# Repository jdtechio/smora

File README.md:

## SMORA

> [Development Blog](http://smora.jdtech.io/)

> Modified from [Minimal Mistakes Jekyll Theme](https://github.com/mmistakes/minimal-mistakes/)

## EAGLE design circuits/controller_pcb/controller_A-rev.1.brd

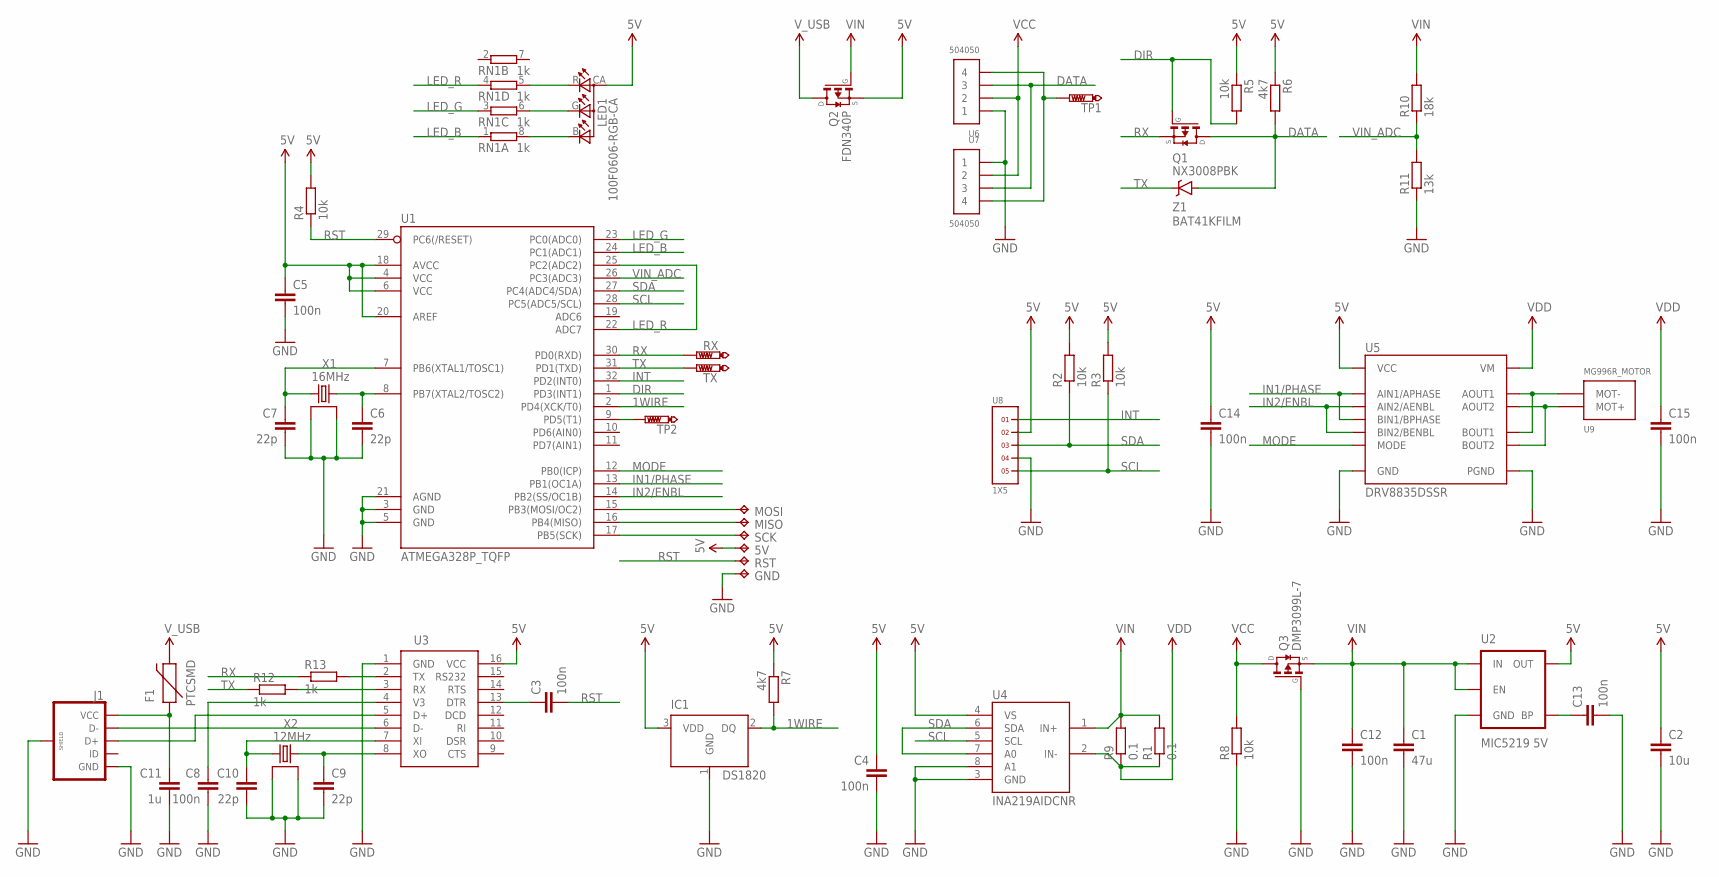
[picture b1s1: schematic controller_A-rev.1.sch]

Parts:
5V: TPTP07SQ; TP07SQ
C1: 47u; C1206
C2: 10u; C0603K
C3, C4, C5, C8, C12, C13, C14, C15: 100n; C0402K
C6, C7, C9, C10: 22p; C0402K
C11: 1u; C0402K
F1: PTCSMD; PTC-1206
GND: TPTP07SQ; TP07SQ
IC1: DS1820; TO-92
J1: USB_MICROB_PLUGCONN-11752; USB-B-MICRO-SMD_V03
LED1: 100F0606-RGB-CA; 1616
MISO: TPTP07SQ; TP07SQ
MOSI: TPTP07SQ; TP07SQ
Q1: NX3008PBK; SSOT-3
Q2: FDN340P; SSOT-3
Q3: DMP3099L-7; SOT23
R1: 0.1; R0603
R2, R3, R4, R5, R8: 10k; R0402
R6, R7: 4k7; R0402
R9: 0.1; R2512
R10: 18k; R0402
R11: 13k; R0402
R12, R13: 1k; R0402
RN1: 1k; YC124
RST: TPTP07SQ; TP07SQ
RX: PTR1TP10R; TP10R
SCK: TPTP07SQ; TP07SQ
TP1, TP2: PTR1TP10R; TP10R
TX: PTR1TP10R; TP10R
U1: ATMEGA328P_TQFP; TQFP32-08
U2: MIC5219 5V; SOT23-5
U3: CH340G; SOIC16
U4: INA219AIDCNR; SOT23-8L
U5: DRV8835DSSR; WSON-12
U6, U7: 504050
U8: 1X5
U9: MG996R_MOTOR; MOTOR
X1: 16MHz; OSC3225
X2: 12MHz; OSC3225
Z1: BAT41KFILM; SOD-523

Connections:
1WIRE: IC1.2 (DQ), R7.2, U1.2 (PD4(XCK/T0))
5V: 5V.TP, C2.1, C4.1, C5.1, C14.1, IC1.3 (VDD), LED1.CA, Q2.2 (S), R2.2, R3.2, R4.2, R5.1, R6.1, R7.1, U1.4 (VCC), U1.6 (VCC), U1.18 (AVCC), U1.20 (AREF), U2.5 (OUT), U3.16 (VCC), U4.4 (VS), U5.P$12 (VCC), U8.2
AUX: TP1.TP, U6.P$4 (4), U7.P$4 (4)
D+: J1.D+, U3.5 (D+)
D-: J1.D-, U3.6 (D-)
DATA: Q1.3 (D), R6.2, U6.P$3 (3), U7.P$3 (3), Z1.P$1 (1)
DIR: Q1.1 (G), R5.2, U1.1 (PD3(INT1))
GND: C1.2, C2.2, C4.2, C5.2, C6.2, C7.2, C8.2, C9.2, C10.2, C11.2, C12.2, C13.2, C14.2, C15.2, GND.TP, IC1.1 (GND), J1.GND, J1.SHIELD1 (SHIELD), J1.SHIELD2 (SHIELD), J1.SHIELD3 (SHIELD), Q3.1 (G), R8.1, R11.1, U1.3 (GND), U1.5 (GND), U1.21 (AGND), U2.2 (GND), U3.1 (GND), U4.3 (GND), U4.8 (A1), U5.P$6 (GND), U5.P$13 (PGND), U5.P$14 (PGND), U5.P$15 (PGND), U5.P$16 (PGND), U6.P$1 (1), U7.P$1 (1), U8.4, X1.P$2 (2), X1.P$4 (4), X2.P$2 (2), X2.P$4 (4)
IN1/PHASE: U1.13 (PB1(OC1A)), U5.P$8 (BIN1/BPHASE), U5.P$10 (AIN1/APHASE)
IN2/ENBL: U1.14 (PB2(SS/OC1B)), U5.P$7 (BIN2/BENBL), U5.P$9 (AIN2/AENBL)
INT: U1.32 (PD2(INT0)), U8.1
LED_B: RN1.1, U1.24 (PC1(ADC1))
LED_B_: LED1.B, RN1.8 (2)
LED_G: RN1.3 (1), U1.23 (PC0(ADC0))
LED_G_: LED1.G, RN1.6 (2)
LED_R: RN1.4 (1), U1.22 (ADC7), U1.25 (PC2(ADC2))
LED_R_: LED1.R, RN1.5 (2)
MODE: U1.12 (PB0(ICP)), U5.P$11 (MODE)
MOT+: U5.P$2 (AOUT1), U5.P$4 (BOUT1), U9.P$3 (MOT-), U9.P$4 (MOT-)
MOT-: U5.P$3 (AOUT2), U5.P$5 (BOUT2), U9.P$1 (MOT+), U9.P$2 (MOT+)
unnamed: C6.1, U1.8 (PB7(XTAL2/TOSC2)), X1.P$1 (1)
unnamed: C7.1, U1.7 (PB6(XTAL1/TOSC1)), X1.P$3 (3)
unnamed: MOSI.TP, U1.15 (PB3(MOSI/OC2))
unnamed: MISO.TP, U1.16 (PB4(MISO))
unnamed: C3.1, U3.13 (DTR)
unnamed: R13.2, U3.2 (TX)
unnamed: C10.1, U3.7 (XI), X2.P$3 (3)
unnamed: C9.1, U3.8 (XO), X2.P$1 (1)
unnamed: C11.1, F1.1, J1.VBUS (VCC)
unnamed: C8.1, U3.4 (V3)
unnamed: C13.1, U2.4 (BP)
unnamed: TP2.TP, U1.9 (PD5(T1))
unnamed: SCK.TP, U1.17 (PB5(SCK))
unnamed: R12.2, U3.3 (RX)
RST: C3.2, R4.1, RST.TP, U1.29 (PC6(/RESET))
RX: Q1.2 (S), R13.1, RX.TP, U1.30 (PD0(RXD))
SCL: R3.1, U1.28 (PC5(ADC5/SCL)), U4.5 (SCL), U8.5
SDA: R2.1, U1.27 (PC4(ADC4/SDA)), U4.6 (SDA), U4.7 (A0), U8.3
TX: R12.1, TX.TP, U1.31 (PD1(TXD)), Z1.P$2 (2)
VCC: Q3.3 (D), R8.2, U6.P$2 (2), U7.P$2 (2)
VDD: C15.1, R1.1, R9.1, U4.2 (IN-), U5.P$1 (VM)
VIN: C1.1, C12.1, Q2.1 (G), Q3.2 (S), R1.2, R9.2, R10.2, U2.1 (IN), U2.3 (EN), U4.1 (IN+)
VIN_ADC: R10.1, R11.2, U1.26 (PC3(ADC3))
V_USB: F1.2, Q2.3 (D)

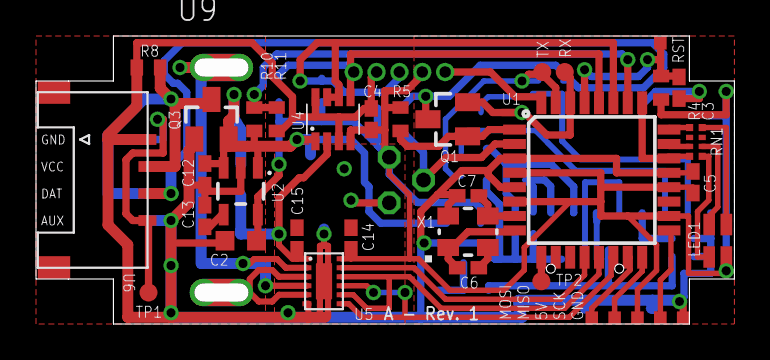
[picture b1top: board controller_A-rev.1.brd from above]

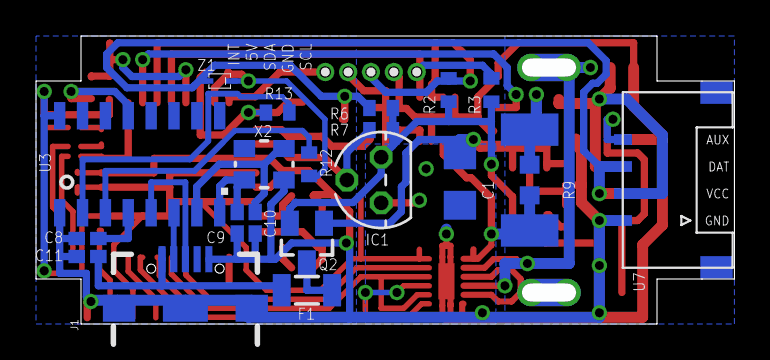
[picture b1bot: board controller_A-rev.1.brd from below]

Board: 2 copper layers, 37.8 x 15.0 mm, 58 parts (22 on the bottom side), 44 nets.

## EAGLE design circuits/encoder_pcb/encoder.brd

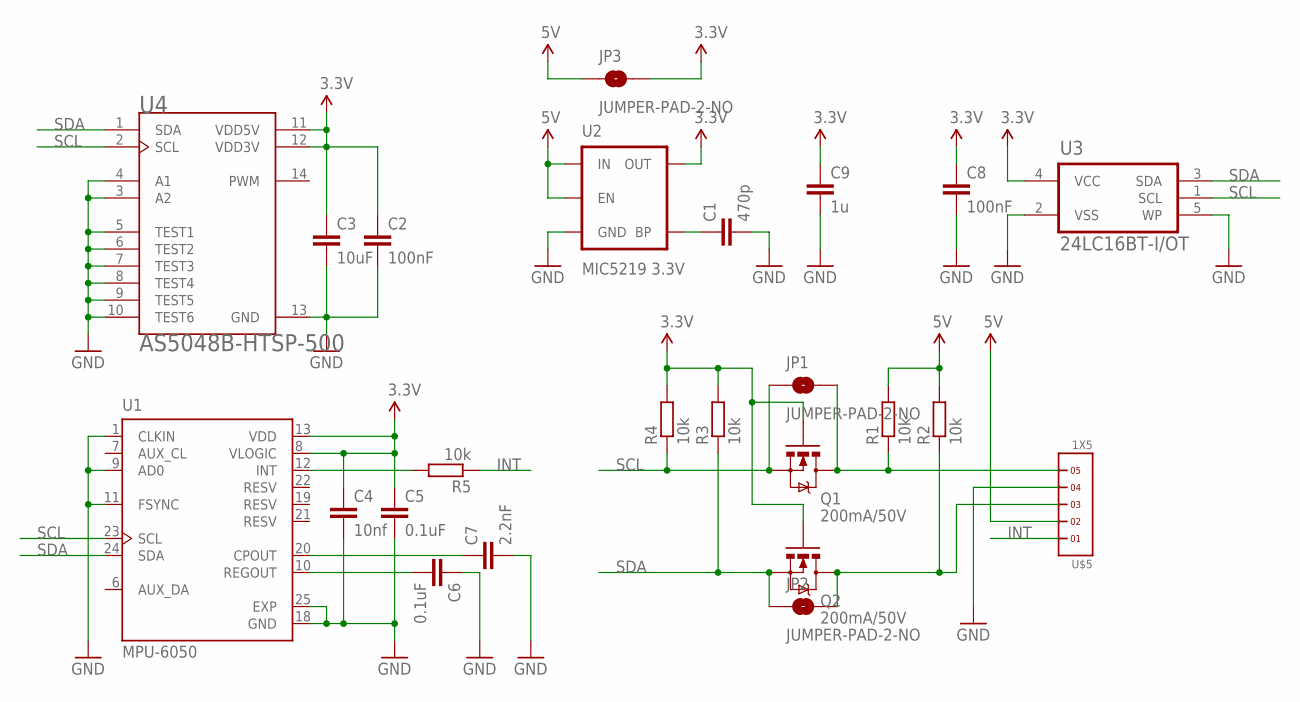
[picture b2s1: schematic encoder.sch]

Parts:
C1: 470p; C0402K
C2, C8: 100nF; C0402K
C3: 10uF; C0603K
C4: 10nf; C0402K
C5, C6: 0.1uF; C0402K
C7: 2.2nF; C0402K
C9: 1u; C0402K
JP1, JP2, JP3: JUMPER-PAD-2-NO; PAD-JUMPER-2-NO_NO_SILK
Q1, Q2: 200mA/50V; SOT23-3
R1, R2, R3, R4, R5: 10k; R0402
U1: MPU-6050; QFN50P400X400X95-25N
U2: MIC5219 3.3V; SOT23-5
U3: 24LC16BT-I/OT; SOT-23-5
U4: AS5048B-HTSP-500; SOP65P640X120-14N
U$5: 1X5

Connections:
3.3V: C2.1, C3.1, C4.1, C5.1, C8.1, C9.1, JP3.2, Q1.1 (G), Q2.1 (G), R3.2, R4.2, U1.8 (VLOGIC), U1.13 (VDD), U2.5 (OUT), U3.4 (VCC), U4.11 (VDD5V), U4.12 (VDD3V)
5V: JP3.1, R1.2, R2.2, U2.1 (IN), U2.3 (EN), U$5.2
GND: C1.2, C2.2, C3.2, C4.2, C5.2, C6.1, C7.2, C8.2, C9.2, U1.1 (CLKIN), U1.9 (AD0), U1.11 (FSYNC), U1.18 (GND), U1.25 (EXP), U2.2 (GND), U3.2 (VSS), U3.5 (WP), U4.3 (A2), U4.4 (A1), U4.5 (TEST1), U4.6 (TEST2), U4.7 (TEST3), U4.8 (TEST4), U4.9 (TEST5), U4.10 (TEST6), U4.13 (GND), U$5.4
INT: R5.1, U$5.1
unnamed: C1.1, U2.4 (BP)
unnamed: C7.1, U1.20 (CPOUT)
unnamed: R5.2, U1.12 (INT)
unnamed: C6.2, U1.10 (REGOUT)
SCL: JP1.1, Q1.2 (S), R4.1, U1.23 (SCL), U3.1 (SCL), U4.2 (SCL)
SCL_: JP1.2, Q1.3 (D), R1.1, U$5.5
SDA: JP2.1, Q2.2 (S), R3.1, U1.24 (SDA), U3.3 (SDA), U4.1 (SDA)
SDA_: JP2.2, Q2.3 (D), R2.1, U$5.3

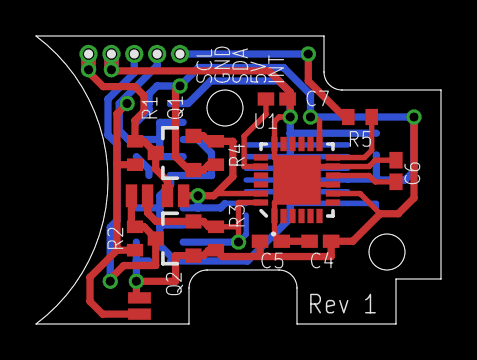
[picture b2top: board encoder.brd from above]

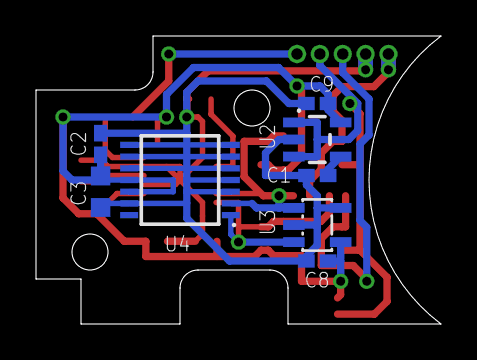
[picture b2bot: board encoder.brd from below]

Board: 2 copper layers, 22.5 x 16.0 mm, 24 parts (8 on the bottom side), 12 nets.

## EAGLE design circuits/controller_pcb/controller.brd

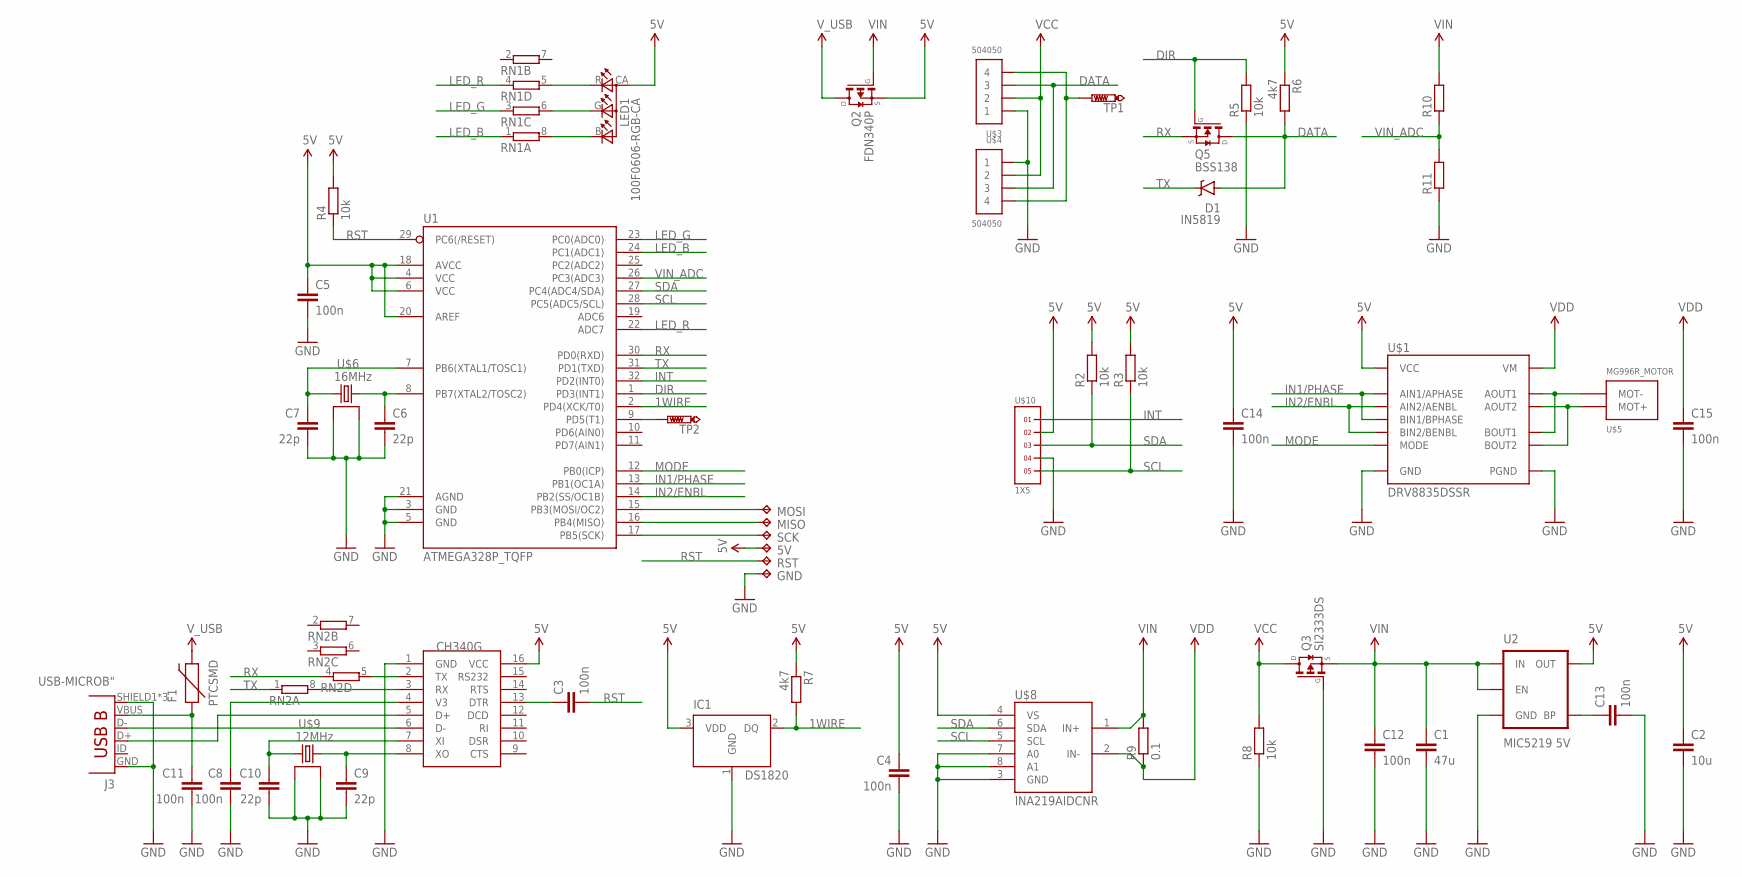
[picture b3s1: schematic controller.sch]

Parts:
5V: TPTP07SQ; TP07SQ
C1: 47u; C1206
C2: 10u; C0603K
C3, C4, C5, C8, C11, C12, C13, C14, C15: 100n; C0402K
C6, C7, C9, C10: 22p; C0402K
D1: IN5819; SMA-DIODE
F1: PTCSMD; PTC-1206
GND: TPTP07SQ; TP07SQ
IC1: DS1820; TO-92
J3: USB-MICROB"; USB-B-MICRO-SMD_V03
LED1: 100F0606-RGB-CA; 1616
MISO: TPTP07SQ; TP07SQ
MOSI: TPTP07SQ; TP07SQ
Q2: FDN340P; SSOT-3
Q3: SI2333DS; SOT23
Q5: BSS138; SOT23
R2, R3, R4, R5, R8: 10k; R0402
R6, R7: 4k7; R0402
R9: 0.1; R2512
R10, R11: R-EU_R0402; R0402
RN1, RN2: 4R-NYC124; YC124
RST: TPTP07SQ; TP07SQ
SCK: TPTP07SQ; TP07SQ
TP1, TP2: PTR1TP12R; TP12R
U1: ATMEGA328P_TQFP; TQFP32-08
U2: MIC5219 5V; SOT23-5
U$1: DRV8835DSSR; WSON-12
U$2: CH340G; SOIC16
U$3, U$4: 504050
U$5: MG996R_MOTOR; MOTOR
U$6: 16MHz; OSC3225
U$8: INA219AIDCNR; SOT23-8L
U$9: 12MHz; OSC3225
U$10: 1X5

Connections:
1WIRE: IC1.2 (DQ), R7.2, U1.2 (PD4(XCK/T0))
5V: 5V.TP, C2.1, C4.1, C5.1, C14.1, IC1.3 (VDD), LED1.CA, Q2.2 (S), R2.2, R3.2, R4.2, R6.1, R7.1, U1.4 (VCC), U1.6 (VCC), U1.18 (AVCC), U1.20 (AREF), U2.5 (OUT), U$1.P$12 (VCC), U$2.16 (VCC), U$8.4 (VS), U$10.2
D+: J3.D+, U$2.5 (D+)
D-: J3.D-, U$2.6 (D-)
DATA: D1.A, Q5.3 (D), R6.2, U$3.P$3 (3), U$4.P$3 (3)
DIR: Q5.1 (G), R5.2, U1.1 (PD3(INT1))
GND: C1.2, C2.2, C4.2, C5.2, C6.2, C7.2, C8.2, C9.2, C10.2, C11.2, C12.2, C13.2, C14.2, C15.2, GND.TP, IC1.1 (GND), J3.GND, J3.SHIELD1 (SHIELD), J3.SHIELD2 (SHIELD), J3.SHIELD3 (SHIELD), Q3.1 (G), R5.1, R8.1, R11.1, U1.3 (GND), U1.5 (GND), U1.21 (AGND), U2.2 (GND), U$1.P$6 (GND), U$1.P$13 (PGND), U$1.P$14 (PGND), U$1.P$15 (PGND), U$1.P$16 (PGND), U$2.1 (GND), U$3.P$1 (1), U$4.P$1 (1), U$6.P$2 (2), U$6.P$4 (4), U$8.3 (GND), U$8.7 (A0), U$8.8 (A1), U$9.P$2 (2), U$9.P$4 (4), U$10.4
IN1/PHASE: U1.13 (PB1(OC1A)), U$1.P$8 (BIN1/BPHASE), U$1.P$10 (AIN1/APHASE)
IN2/ENBL: U1.14 (PB2(SS/OC1B)), U$1.P$7 (BIN2/BENBL), U$1.P$9 (AIN2/AENBL)
INT: U1.32 (PD2(INT0)), U$10.1
LED_B: RN1.1, U1.24 (PC1(ADC1))
LED_B_: LED1.B, RN1.8 (2)
LED_G: RN1.3 (1), U1.23 (PC0(ADC0))
LED_G_: LED1.G, RN1.6 (2)
LED_R: RN1.4 (1), U1.22 (ADC7)
LED_R_: LED1.R, RN1.5 (2)
MODE: U1.12 (PB0(ICP)), U$1.P$11 (MODE)
MOT+: U$1.P$2 (AOUT1), U$1.P$4 (BOUT1), U$5.P$3 (MOT-), U$5.P$4 (MOT-)
MOT-: U$1.P$3 (AOUT2), U$1.P$5 (BOUT2), U$5.P$1 (MOT+), U$5.P$2 (MOT+)
unnamed: C6.1, U1.8 (PB7(XTAL2/TOSC2)), U$6.P$1 (1)
unnamed: C7.1, U1.7 (PB6(XTAL1/TOSC1)), U$6.P$3 (3)
unnamed: MOSI.TP, U1.15 (PB3(MOSI/OC2))
unnamed: MISO.TP, U1.16 (PB4(MISO))
unnamed: C3.1, U$2.13 (DTR)
unnamed: RN2.5 (2), U$2.2 (TX)
unnamed: TP1.TP, U$3.P$4 (4), U$4.P$4 (4)
unnamed: C10.1, U$2.7 (XI), U$9.P$3 (3)
unnamed: C9.1, U$2.8 (XO), U$9.P$1 (1)
unnamed: C11.1, F1.1, J3.VBUS
unnamed: C8.1, U$2.4 (V3)
unnamed: C13.1, U2.4 (BP)
unnamed: TP2.TP, U1.9 (PD5(T1))
unnamed: SCK.TP, U1.17 (PB5(SCK))
unnamed: RN2.8 (2), U$2.3 (RX)
RST: C3.2, R4.1, RST.TP, U1.29 (PC6(/RESET))
RX: Q5.2 (S), RN2.4 (1), U1.30 (PD0(RXD))
SCL: R3.1, U1.28 (PC5(ADC5/SCL)), U$8.5 (SCL), U$10.5
SDA: R2.1, U1.27 (PC4(ADC4/SDA)), U$8.6 (SDA), U$10.3
TX: D1.C, RN2.1, U1.31 (PD1(TXD))
VCC: Q3.3 (D), R8.2, U$3.P$2 (2), U$4.P$2 (2)
VDD: C15.1, R9.1, U$1.P$1 (VM), U$8.2 (IN-)
VIN: C1.1, C12.1, Q2.1 (G), Q3.2 (S), R9.2, R10.2, U2.1 (IN), U2.3 (EN), U$8.1 (IN+)
VIN_ADC: R10.1, R11.2, U1.26 (PC3(ADC3))
V_USB: F1.2, Q2.3 (D)

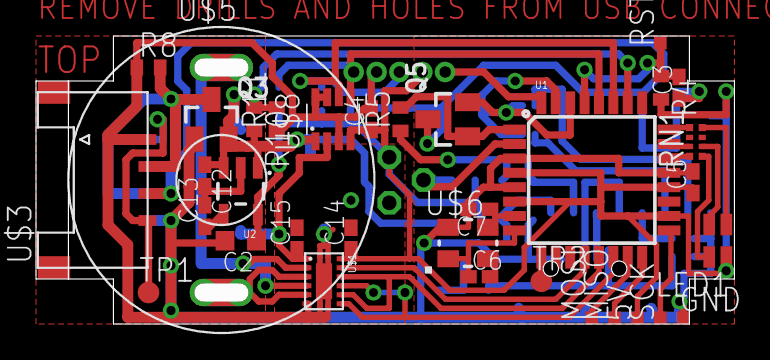
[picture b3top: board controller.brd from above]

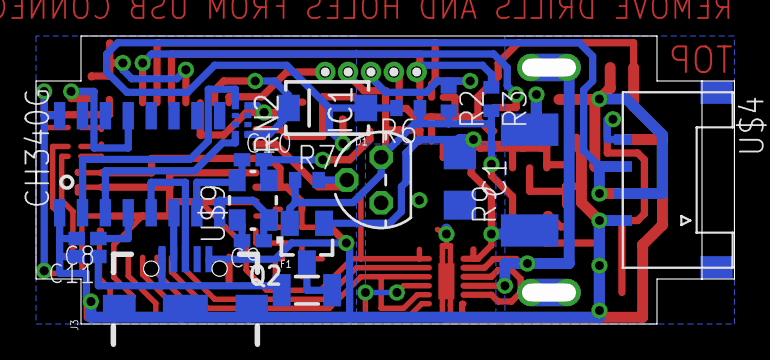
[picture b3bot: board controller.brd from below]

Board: 2 copper layers, 37.8 x 15.0 mm, 54 parts (20 on the bottom side), 44 nets.

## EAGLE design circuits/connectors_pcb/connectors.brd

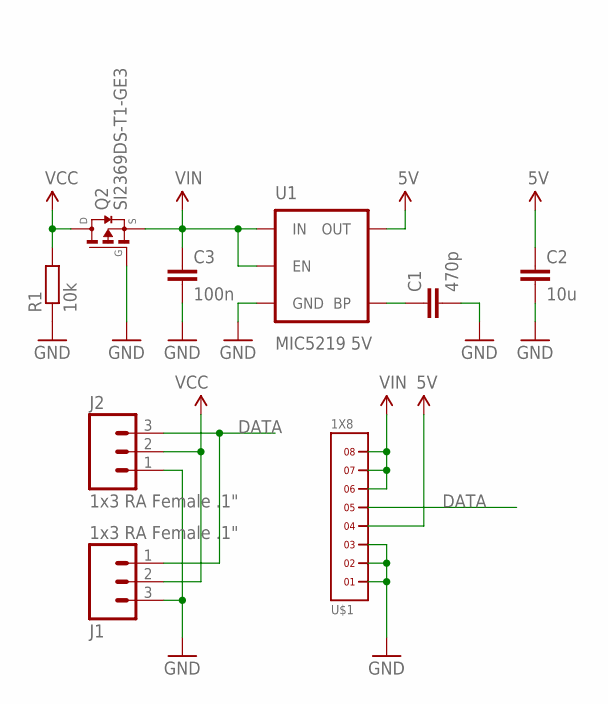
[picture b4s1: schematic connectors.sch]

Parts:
C1: 470p; C0402K
C2: 10u; C0603K
C3: 100n; C0402K
J1, J2: 1x3 RA Female .1"; 1X03_SMD_RA_FEMALE
Q2: SI2369DS-T1-GE3; SOT23
R1: 10k; R0603
U1: MIC5219 5V; SOT23-5
U$1: 1X8

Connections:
5V: C2.1, U1.5 (OUT), U$1.4
DATA: J1.1, J2.3, U$1.5
GND: C1.2, C2.2, C3.2, J1.3, J2.1, Q2.1 (G), R1.1, U1.2 (GND), U$1.1, U$1.2, U$1.3
unnamed: C1.1, U1.4 (BP)
VCC: J1.2, J2.2, Q2.3 (D), R1.2
VIN: C3.1, Q2.2 (S), U1.1 (IN), U1.3 (EN), U$1.6, U$1.7, U$1.8

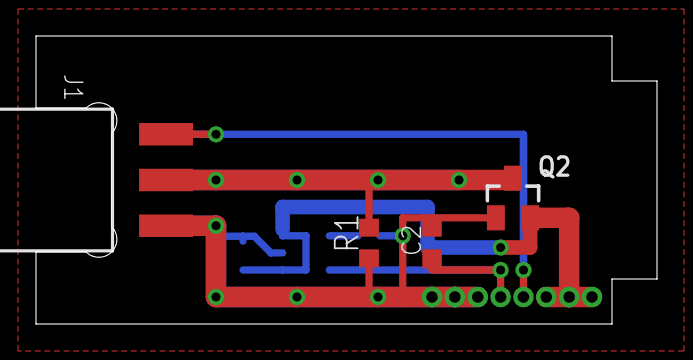
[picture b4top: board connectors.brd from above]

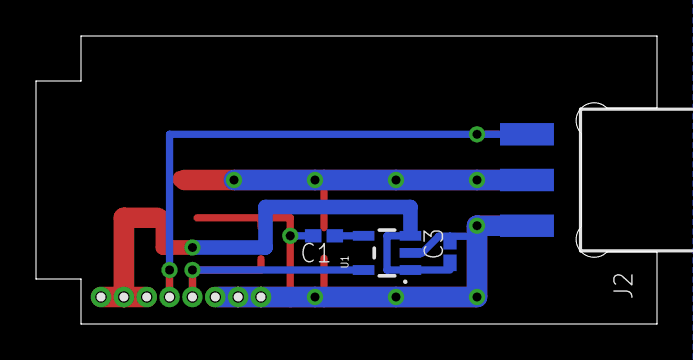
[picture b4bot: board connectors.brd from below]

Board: 2 copper layers, 34.5 x 16.0 mm, 9 parts (5 on the bottom side), 6 nets.

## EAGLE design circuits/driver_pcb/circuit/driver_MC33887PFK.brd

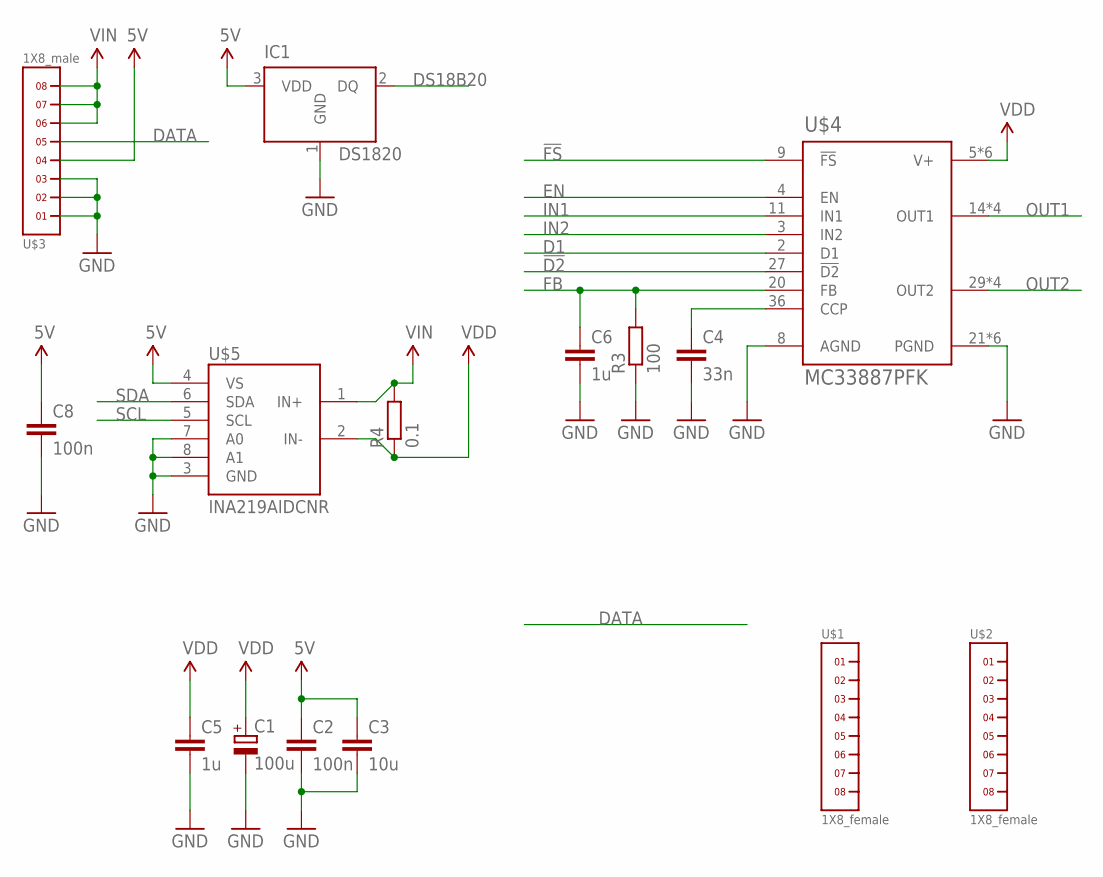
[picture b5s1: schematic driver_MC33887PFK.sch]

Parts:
C1: 100u; PANASONIC_D
C2, C8: 100n; C0402K
C3: 10u; C0603K
C4: 33n; C0402K
C5, C6: 1u; C0402K
IC1: DS1820; TO-92
R3: 100; R0402
R4: 0.1; R0603
U$1, U$2: 1X8_female; 1X8
U$3: 1X8_male; 1X8_MALE
U$4: MC33887PFK; QFN32
U$5: INA219AIDCNR; SOT23-8L

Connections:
5V: C2.1, C3.1, C8.1, IC1.3 (VDD), U$3.4, U$5.4 (VS)
!D2: U$4.27 (!D2)
!FS: U$4.9 (!FS)
D1: U$4.2 (D1)
DATA: U$3.5
DS18B20: IC1.2 (DQ)
EN: U$4.4 (EN)
FB: C6.1, R3.2, U$4.20 (FB)
GND: C1.-, C2.2, C3.2, C4.2, C5.2, C6.2, C8.2, IC1.1 (GND), R3.1, U$3.1, U$3.2, U$3.3, U$4.8 (AGND), U$4.21 (PGND), U$4.22 (PGND), U$4.23 (PGND), U$4.24 (PGND), U$4.25 (PGND), U$4.26 (PGND), U$5.3 (GND), U$5.7 (A0), U$5.8 (A1)
IN1: U$4.11 (IN1)
IN2: U$4.3 (IN2)
unnamed: C4.1, U$4.36 (CCP)
OUT1: U$4.14 (OUT1), U$4.15 (OUT1), U$4.17 (OUT1), U$4.18 (OUT1)
OUT2: U$4.29 (OUT2), U$4.30 (OUT2), U$4.32 (OUT2), U$4.33 (OUT2)
SCL: U$5.5 (SCL)
SDA: U$5.6 (SDA)
VDD: C1.+, C5.1, R4.1, U$4.5 (V+), U$4.6 (V+), U$4.12 (V+), U$4.13 (V+), U$4.34 (V+), U$4.35 (V+), U$5.2 (IN-)
VIN: R4.2, U$3.6, U$3.7, U$3.8, U$5.1 (IN+)

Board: 2 copper layers, 15 parts (4 on the bottom side), 8 nets, no tracks yet.

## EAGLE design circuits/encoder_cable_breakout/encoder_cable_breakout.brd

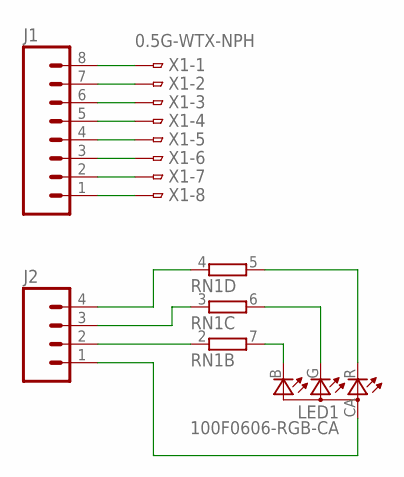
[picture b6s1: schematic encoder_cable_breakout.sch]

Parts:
J1: M08SILK_FEMALE_PTH; 1X08
J2: M04PTH; 1X04
LED1: 100F0606-RGB-CA; 1616
RN1: 4R-NYC124; YC124
X1: 0.5G-WTX-NPH; 0.5G-WTX-NP

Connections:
unnamed: J1.8, X1.1
unnamed: J1.7, X1.2
unnamed: J1.6, X1.3
unnamed: J1.5, X1.4
unnamed: J1.4, X1.5
unnamed: J1.3, X1.6
unnamed: J1.2, X1.7
unnamed: J1.1, X1.8
unnamed: J2.3, RN1.3 (1)
unnamed: J2.2, RN1.2 (1)
unnamed: J2.4, RN1.4 (1)
unnamed: J2.1, LED1.CA
unnamed: LED1.R, RN1.5 (2)
unnamed: LED1.G, RN1.6 (2)
unnamed: LED1.B, RN1.7 (2)

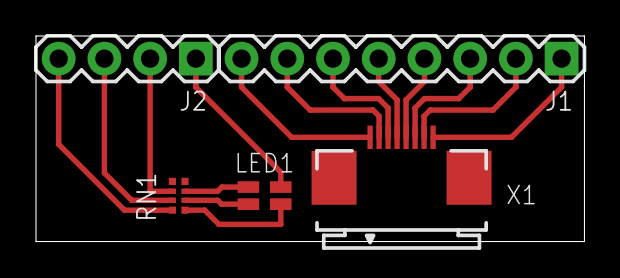
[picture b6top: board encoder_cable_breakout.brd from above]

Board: 2 copper layers, 30.5 x 11.4 mm, 5 parts (0 on the bottom side), 15 nets.

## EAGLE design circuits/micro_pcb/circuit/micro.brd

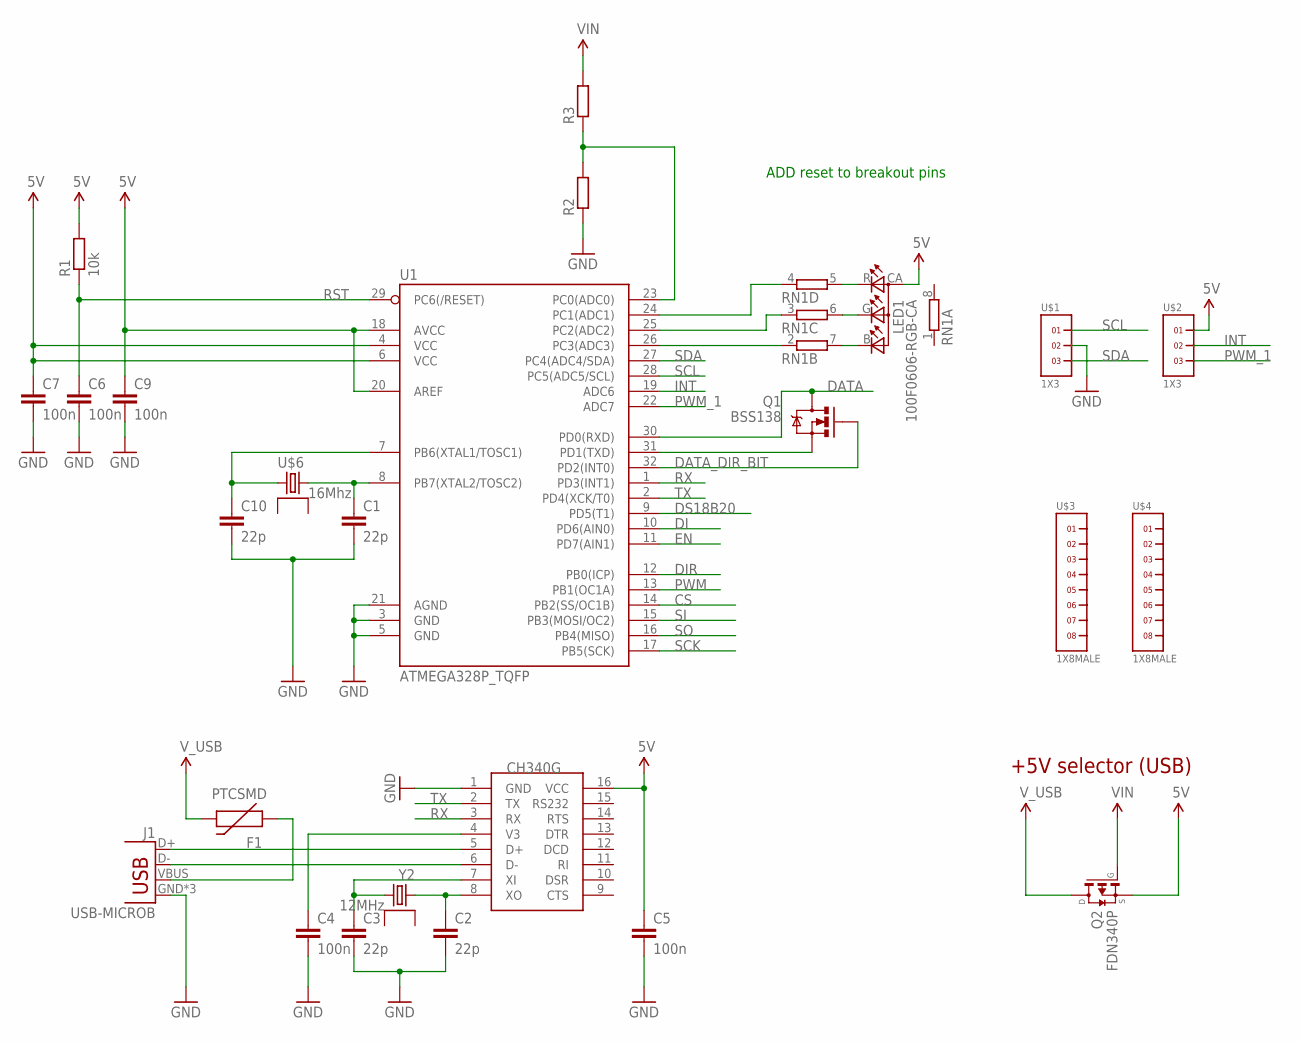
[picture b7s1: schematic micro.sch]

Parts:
C1, C2, C3, C10: 22p; C0402K
C4, C5, C6, C7, C9: 100n; C0402K
F1: PTCSMD; PTC-1206
J1: USB-MICROB
LED1: 100F0606-RGB-CA; 1616
Q1: BSS138; SOT23-3
Q2: FDN340P; SSOT-3
R1: 10k; R0402
R2, R3: R-EU_R0402; R0402
RN1: 4R-NYC124; YC124
U1: ATMEGA328P_TQFP; TQFP32-08
U$1, U$2: 1X3
U$3, U$4: 1X8MALE; 1X8_MALE
U$5: CH340G; SOIC16
U$6: 16Mhz; OSC3225
Y2: 12MHz; GSX-531

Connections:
5V: C5.1, C7.1, C9.1, LED1.CA, Q2.2 (S), R1.2, U1.4 (VCC), U1.6 (VCC), U1.18 (AVCC), U1.20 (AREF), U$2.1, U$5.16 (VCC)
CS: U1.14 (PB2(SS/OC1B))
D+: J1.D+, U$5.5 (D+)
D-: J1.D-, U$5.6 (D-)
DATA: Q1.3 (D), U1.30 (PD0(RXD))
DATA_DIR_BIT: Q1.1 (G), U1.32 (PD2(INT0))
DI: U1.10 (PD6(AIN0))
DIR: U1.12 (PB0(ICP))
DS18B20: U1.9 (PD5(T1))
EN: U1.11 (PD7(AIN1))
GND: C1.2, C2.2, C3.2, C4.2, C5.2, C6.2, C7.2, C9.2, C10.2, J1.GND, J1.MT1 (GND), J1.MT2 (GND), R2.1, U1.3 (GND), U1.5 (GND), U1.21 (AGND), U$1.2, U$5.1 (GND)
INT: U1.19 (ADC6), U$2.2
unnamed: C2.1, U$5.8 (XO), Y2.P$1 (1)
unnamed: C3.1, U$5.7 (XI), Y2.P$3 (3)
unnamed: C1.1, U1.8 (PB7(XTAL2/TOSC2)), U$6.P$3 (3)
unnamed: C4.1, U$5.4 (V3)
unnamed: C10.1, U1.7 (PB6(XTAL1/TOSC1)), U$6.P$1 (1)
unnamed: F1.1, J1.VBUS
unnamed: Q1.2 (S), U1.31 (PD1(TXD))
unnamed: R2.2, R3.1, U1.23 (PC0(ADC0))
unnamed: RN1.2 (1), U1.26 (PC3(ADC3))
unnamed: RN1.3 (1), U1.25 (PC2(ADC2))
unnamed: RN1.4 (1), U1.24 (PC1(ADC1))
unnamed: LED1.R, RN1.5 (2)
unnamed: LED1.G, RN1.6 (2)
unnamed: LED1.B, RN1.7 (2)
PWM: U1.13 (PB1(OC1A))
PWM_1: U1.22 (ADC7), U$2.3
RST: C6.1, R1.1, U1.29 (PC6(/RESET))
RX: U1.1 (PD3(INT1)), U$5.3 (RX)
SCK: U1.17 (PB5(SCK))
SCL: U1.28 (PC5(ADC5/SCL)), U$1.1
SDA: U1.27 (PC4(ADC4/SDA)), U$1.3
SI: U1.15 (PB3(MOSI/OC2))
SO: U1.16 (PB4(MISO))
TX: U1.2 (PD4(XCK/T0)), U$5.2 (TX)
VIN: Q2.1 (G), R3.2
V_USB: F1.2, Q2.3 (D)

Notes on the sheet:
+5V selector (USB)
ADD reset to breakout pins

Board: 2 copper layers, 26 parts (3 on the bottom side), 29 nets, no tracks yet.

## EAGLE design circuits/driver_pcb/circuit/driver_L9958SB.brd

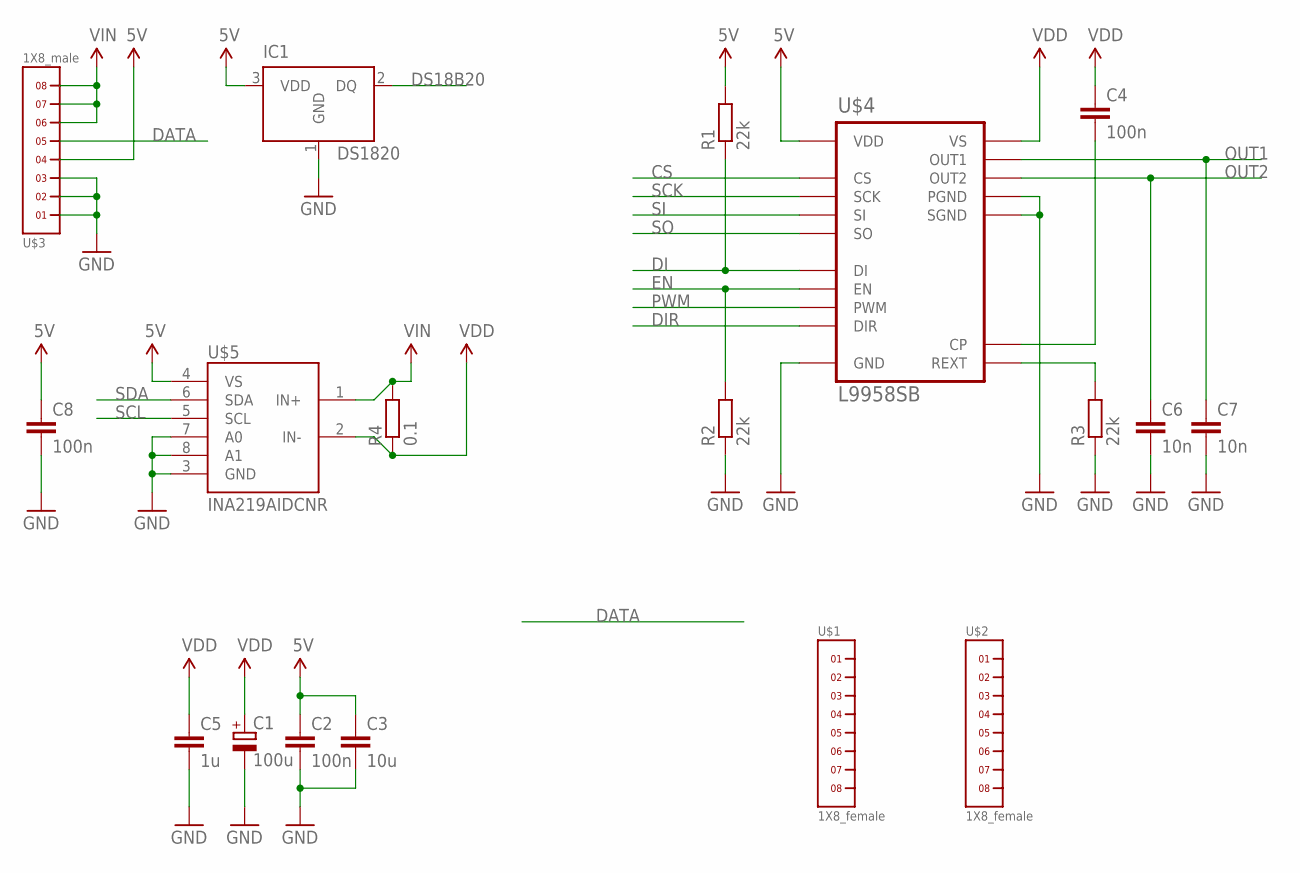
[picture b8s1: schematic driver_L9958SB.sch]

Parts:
C1: 100u; PANASONIC_D
C2, C4, C8: 100n; C0402K
C3: 10u; C0603K
C5: 1u; C0402K
C6, C7: 10n; C0402K
IC1: DS1820; TO-92
R1, R2, R3: 22k; R0402
R4: 0.1; R0603
U$1, U$2: 1X8_female; 1X8
U$3: 1X8_male; 1X8_MALE
U$4: L9958SB; POWERSO16
U$5: INA219AIDCNR; SOT23-8L

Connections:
5V: C2.1, C3.1, C8.1, IC1.3 (VDD), R1.2, U$3.4, U$4.P$16 (VDD), U$5.4 (VS)
CS: U$4.P$3 (CS)
DATA: U$3.5
DI: R1.1, U$4.P$7 (DI)
DIR: U$4.P$5 (DIR)
DS18B20: IC1.2 (DQ)
EN: R2.2, U$4.P$9 (EN)
GND: C1.-, C2.2, C3.2, C5.2, C6.2, C7.2, C8.2, IC1.1 (GND), R2.1, R3.1, U$3.1, U$3.2, U$3.3, U$4.P$1 (GND), U$4.P$8 (PGND), U$4.P$17 (SGND), U$5.3 (GND), U$5.7 (A0), U$5.8 (A1)
unnamed: C4.2, U$4.P$4 (CP)
unnamed: R3.2, U$4.P$12 (REXT)
OUT1: C7.1, U$4.P$6 (OUT1)
OUT2: C6.1, U$4.P$10 (OUT2)
PWM: U$4.P$11 (PWM)
SCK: U$4.P$15 (SCK)
SCL: U$5.5 (SCL)
SDA: U$5.6 (SDA)
SI: U$4.P$14 (SI)
SO: U$4.P$2 (SO)
VDD: C1.+, C4.1, C5.1, R4.1, U$4.P$13 (VS), U$5.2 (IN-)
VIN: R4.2, U$3.6, U$3.7, U$3.8, U$5.1 (IN+)

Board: 2 copper layers, 18 parts (4 on the bottom side), 10 nets, no tracks yet.

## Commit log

2016-08-01 Added .gitignore
2016-08-16 Unified gh-pages blog into single repository
2016-08-16 Manually deleted CNAME
2016-08-16 Create CNAME
2016-08-18 Added Encoder Eagle files and 3D parts STL files
2016-08-18 Added Encoder cable breakout Eagle files
2016-08-18 Added AS5048B arduino test sketch
2016-08-18 Added DS18B20 arduino test sketch
2016-08-18 Added MPU6050 arduino and processing test sketch
2016-08-18 Added post 2016-08-16-magnetic-encoder-pcb.md
2016-08-18 Updated 2016-08-16-magnetic-encoder-pcb.md post
2016-08-18 README update
2016-08-19 Added Fusion 360 magnetic encoder model files
2016-08-21 Corrected 2016-08-16-magnetic-encoder-pcb.md post for some spelling mistakes
2016-09-06 Removed obsolete encoder breakout board
2016-09-06 Updated encoder PCB - UNTESTED
2016-09-06 Added connectors PCB - UNTESTED
2016-09-06 Added driver PCB - UNTESTED
    Untested boards for the L9958SB and MC33887PFK drivers
2016-09-06 Added microcontroller PCB - UNTESTED
2016-09-06 Added untested schematics
2016-09-09 Minor updates to schematic and board files. Still UNTESTED
2016-09-18 Removed obsolete designs
2016-09-18 Merged multiple board into a single one - controller - UNTESTED
2016-09-18 Updated encoder board - UNTESTED
2016-09-18 Removed obsolete schematics
2016-09-18 Added encoder schematic and board picture
2016-09-19 Updated controller circuit - UNTESTED
2016-09-19 Updated controller pictures
2016-09-20 Corrected Q5 orientation - UNTESTED
2016-09-21 Updated encoder pictures
2016-09-21 Updated encoder to revision 1 - UNTESTED
2016-09-21 Updated controller Version A to Revision 1 - UNTESTED
2016-09-21 Updated controller Version A pictures
2016-09-25 Updated Q1 and replaced schottky diode - UNTESTED
2016-10-27 Updated encoder PCB - Tested and working
2016-10-27 Updated controller PCB - Tested and working
2016-10-27 Updated controller A-rev.1 schematic and board pictures
2016-10-27 Updated encoder schematic and board pictures
2016-10-27 Added encoder pcb 3D model
2016-10-27 Added controller pcb 3D model
2016-11-30 SMORA's arduino library - first commit
2016-12-03 Removed SMORA library - current code can be found in the smora-code repository

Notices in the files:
parts and their libraries:
SparkFun-Connectors: Licensing: Creative Commons ShareAlike 4.0 International - https://creativecommons.org/licenses/by-sa/4.0
crystals_golledge_full_v1-0: © Golledge Electronics Ltd 2015. Released under GNU General Public License. Full library V1.0.
